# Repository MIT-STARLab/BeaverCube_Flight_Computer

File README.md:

# Note
This board is still under test, we will be updating system operational status as tests are completed.

# BFC
The BeaverCube Flight Computer, or CASTOR Pi Board, is an open-source flight computer for CubeSats. Designed for the MIT BeaverCube CubeSat mission, the board supports an imaging payload with 3 cameras over USB as well as subsystem boards over UART, I2C and SPI buses. 

CASTOR Pi Board: CubeSat Atmospheric and Sea-surface Temperature Optical Observation Raspberry Pi Board

# Known Issues, Testing Progress
The BFC rev 1.0 is currently being tested, with rev 2.0 expected to be manufactured and testing started by the end of August 2020. The power system has been characterized under expected loads and is fully operational with no errors detected. The RPI recovery system (see schematic Sheet 3) that controls which RPI is running and SD card is selected has been fully tested, and no errors detected.

The USB hub is currently under test to verify all ports can communicate with the compute module. Additional tests to be completed by mid-July 2020 include running flight software to verify all onboard devices (RTC, IMUs) function nominally, and interfacing the BFC with devices to test external connections including RS-485, TTL UART, I2C, SPI.

Known errors on rev 1.0 that will be fixed in rev 2.0
- SD card MUXs U4, U11, U13, U14 have incorrect footprints. The compute module cannot access the SD card slots.
- The USB line is routed to the incorrect GPIO pin on the compute module. A temporary fix was made to continue testing.

# project
Eagle CAD Project, Board, Schematic files.

# libraries
Ealgle CAD Library files.

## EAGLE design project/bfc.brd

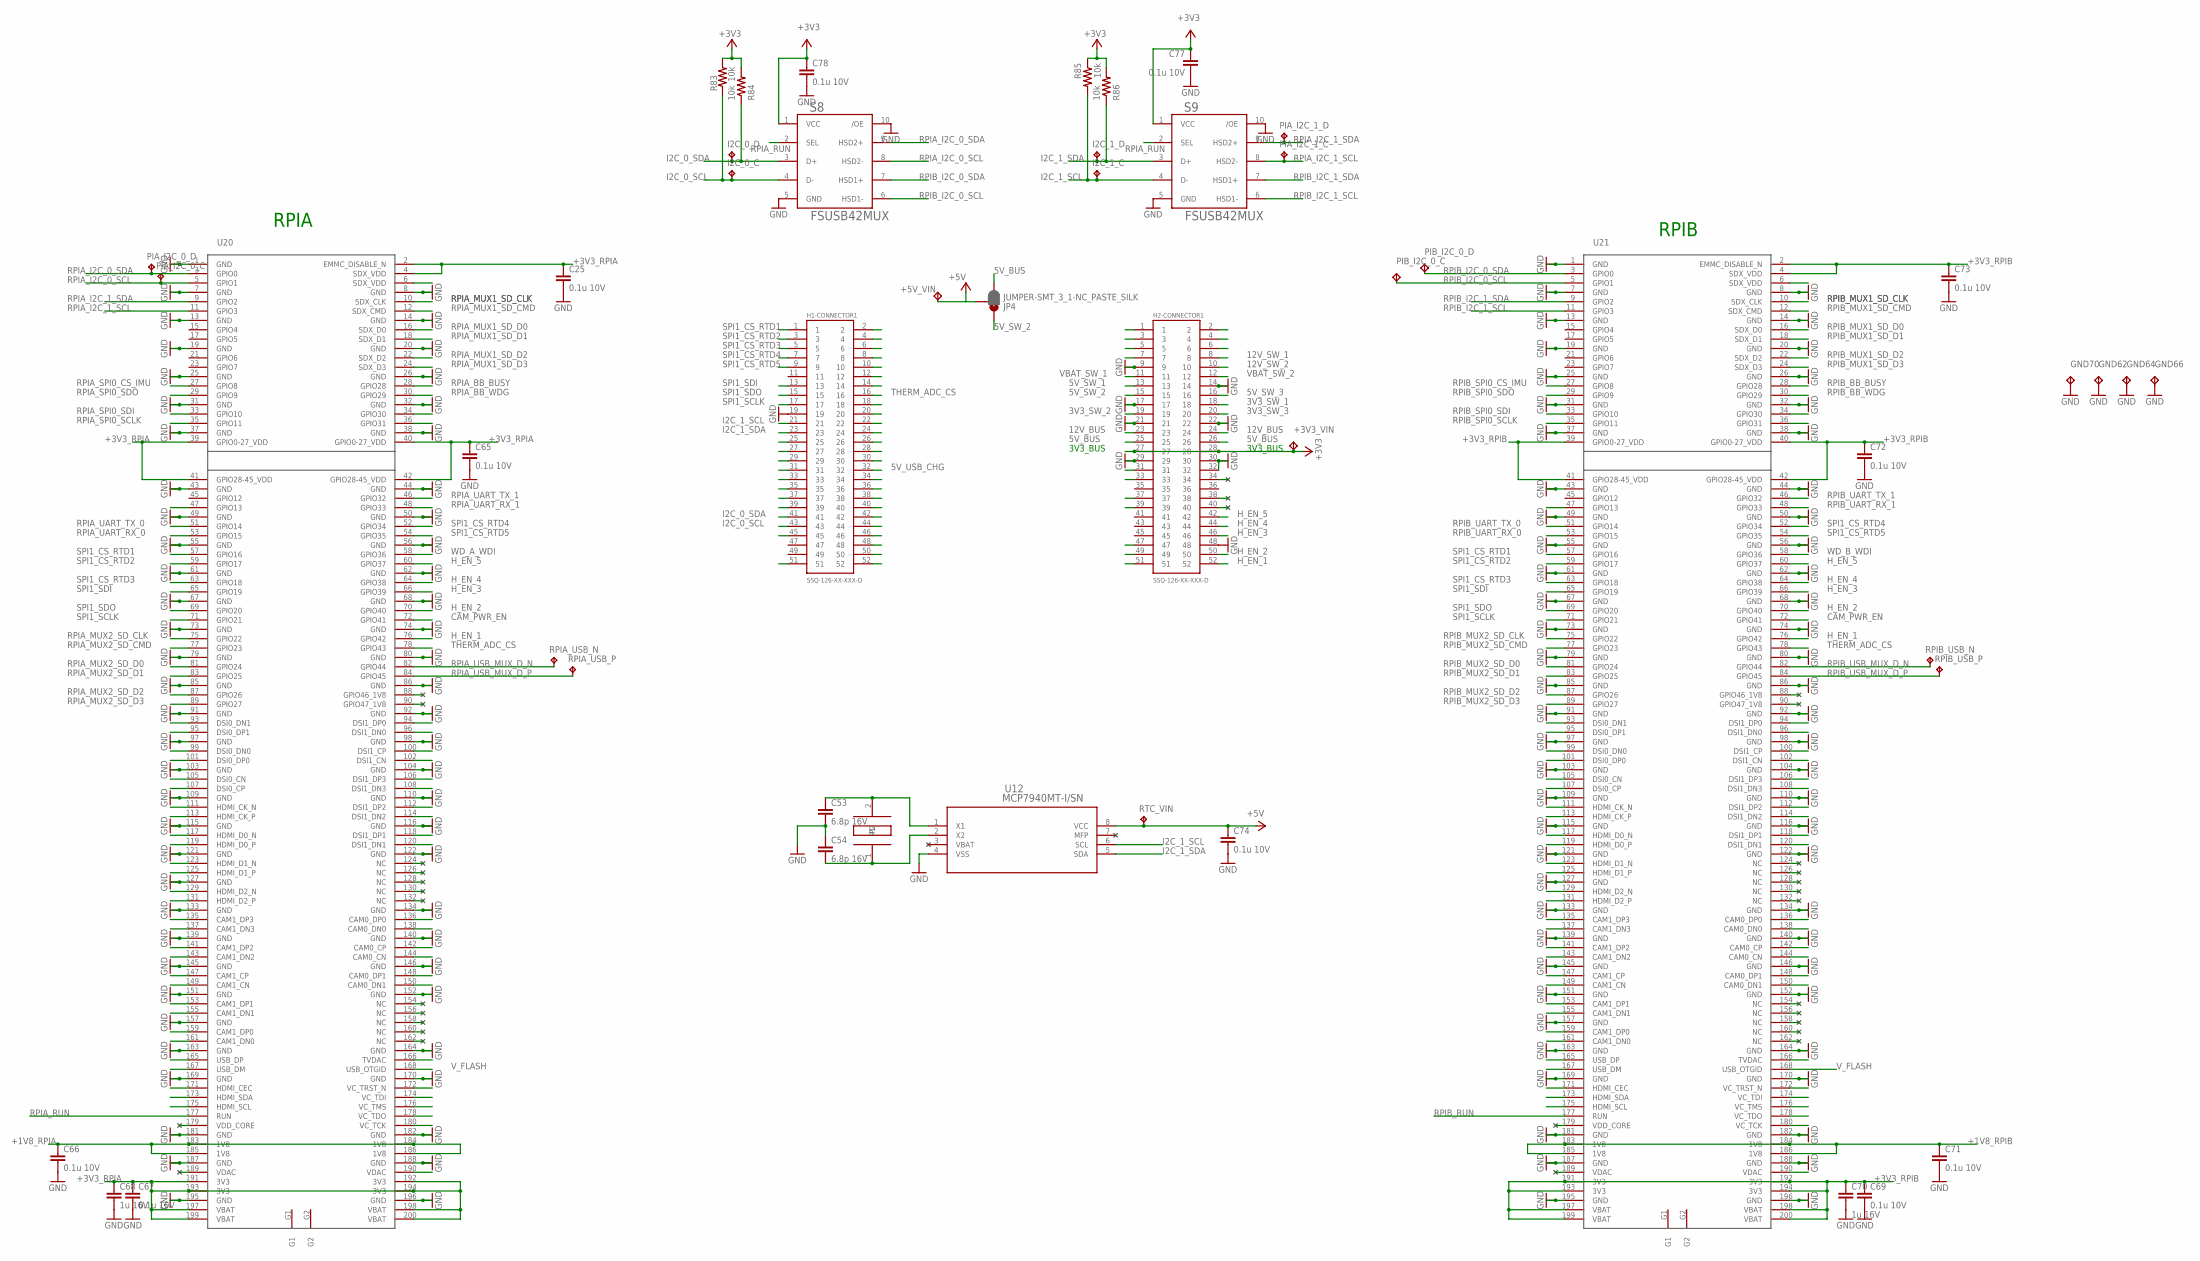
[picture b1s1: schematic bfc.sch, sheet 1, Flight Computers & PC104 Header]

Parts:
+3V3_VIN, +5V_VIN: TP_HRWN; MPN S2751-46R
C25, C65, C66, C67, C69, C71, C72, C73, C74, C77, C78: 0.1u 10V; C0603
C53, C54: 6.8p 16V; C0603
C68, C70: 1u 16V; C0603
GND62, GND64, GND66, GND70: TP_HRWN; MPN S2751-46R
H1-CONNECTOR1, H2-CONNECTOR1: SSQ-126-XX-XXX-D; MPN SSQ-126-23-G-D
I2C_0_C, I2C_0_D, I2C_1_C, I2C_1_D: TPB1,27; B1,27
JP4: JUMPER-SMT_3_1-NC_PASTE_SILK; SMT-JUMPER_3_1-NC_PASTE_SILK
PIA_I2C_0_C, PIA_I2C_0_D, PIA_I2C_1_C, PIA_I2C_1_D: TPB1,27; B1,27
PIB_I2C_0_C, PIB_I2C_0_D: TP_HRWN; MPN S2751-46R
R83, R84, R85, R86: 10k; R0603
RPIA_USB_N: TPB1,27; B1,27
RPIA_USB_P: TPB1,27; B1,27
RPIB_USB_N: TPB1,27; B1,27
RPIB_USB_P: TPB1,27; B1,27
RTC_VIN: TPB1,27; B1,27
S8, S9: FSUSB42MUX; MPN FSUSB42MUX
U12: MCP7940MT-I/SN; SOIC8-N_MC; MPN MCP7940MT-I/SN
U20, U21: COMPUTE_MODULE; SO-DIMM; MPN 1473005-4
X4: TC-135; MPN FC-135 32.768KA-AG0

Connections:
3V3_SW_1: H2-CONNECTOR1.18
3V3_SW_2: H2-CONNECTOR1.19; also elsewhere on the board
3V3_SW_3: H2-CONNECTOR1.20; also elsewhere on the board
5V_BUS: H2-CONNECTOR1.25, H2-CONNECTOR1.26, JP4.3; also elsewhere on the board
5V_SW_1: H2-CONNECTOR1.13
5V_SW_2: H2-CONNECTOR1.15, JP4.1
5V_SW_3: H2-CONNECTOR1.16
5V_USB_CHG: H1-CONNECTOR1.32
12V_BUS: H2-CONNECTOR1.23, H2-CONNECTOR1.24; also elsewhere on the board
12V_SW_1: H2-CONNECTOR1.8; also elsewhere on the board
12V_SW_2: H2-CONNECTOR1.10
+1V8_RPIA: C66.1, U20.183 (1V8), U20.184 (1V8), U20.185 (1V8), U20.186 (1V8); also elsewhere on the board
+1V8_RPIB: C71.1, U21.183 (1V8), U21.184 (1V8), U21.185 (1V8), U21.186 (1V8); also elsewhere on the board
+3V3: +3V3_VIN.P$1, C77.1, C78.1, H2-CONNECTOR1.27, H2-CONNECTOR1.28, R83.2, R84.2, R85.1, R86.2, S8.1 (VCC), S9.1 (VCC); also elsewhere on the board
+3V3_RPIA: C25.1, C65.1, C67.1, C68.1, U20.2 (EMMC_DISABLE_N), U20.4 (SDX_VDD), U20.39 (GPIO0-27_VDD), U20.40 (GPIO0-27_VDD), U20.41 (GPIO28-45_VDD), U20.42 (GPIO28-45_VDD), U20.191 (3V3), U20.192 (3V3), U20.193 (3V3), U20.194 (3V3), U20.197 (VBAT), U20.198 (VBAT), U20.199 (VBAT), U20.200 (VBAT); also elsewhere on the board
+3V3_RPIB: C69.1, C70.1, C72.1, C73.1, U21.2 (EMMC_DISABLE_N), U21.4 (SDX_VDD), U21.39 (GPIO0-27_VDD), U21.40 (GPIO0-27_VDD), U21.41 (GPIO28-45_VDD), U21.42 (GPIO28-45_VDD), U21.191 (3V3), U21.192 (3V3), U21.193 (3V3), U21.194 (3V3), U21.197 (VBAT), U21.198 (VBAT), U21.199 (VBAT), U21.200 (VBAT); also elsewhere on the board
+5V: +5V_VIN.P$1, C74.1, JP4.2, RTC_VIN.TP, U12.8 (VCC); also elsewhere on the board
CAM_PWR_EN: U20.72 (GPIO41), U21.72 (GPIO41); also elsewhere on the board
GND: C25.2, C53.2, C54.1, C65.2, C66.2, C67.2, C68.2, C69.2, C70.2, C71.2, C72.2, C73.2, C74.2, C77.2, C78.2, GND62.P$1, GND64.P$1, GND66.P$1, GND70.P$1, H1-CONNECTOR1.19, H2-CONNECTOR1.9, H2-CONNECTOR1.14, H2-CONNECTOR1.17, H2-CONNECTOR1.21, H2-CONNECTOR1.22, H2-CONNECTOR1.29, H2-CONNECTOR1.30, H2-CONNECTOR1.32, H2-CONNECTOR1.48, S8.5 (GND), S8.10 (/OE), S9.5 (GND), S9.10 (/OE), U12.4 (VSS), U20.1 (GND), U20.7 (GND), U20.8 (GND), U20.13 (GND), U20.14 (GND), U20.19 (GND), U20.20 (GND), U20.25 (GND), U20.26 (GND), U20.31 (GND), U20.32 (GND), U20.37 (GND), U20.38 (GND), U20.43 (GND), U20.44 (GND), U20.49 (GND), U20.50 (GND), U20.55 (GND), U20.56 (GND), U20.61 (GND), U20.62 (GND), U20.67 (GND), U20.68 (GND), U20.73 (GND), U20.74 (GND), U20.79 (GND), U20.80 (GND), U20.85 (GND), U20.86 (GND), U20.91 (GND), U20.92 (GND), U20.97 (GND), U20.98 (GND), U20.103 (GND), U20.104 (GND), U20.109 (GND), U20.110 (GND), U20.115 (GND), U20.116 (GND), U20.121 (GND), U20.122 (GND), U20.127 (GND), U20.133 (GND), U20.134 (GND), U20.139 (GND), U20.140 (GND), U20.145 (GND), U20.146 (GND), U20.151 (GND), U20.152 (GND), U20.157 (GND), U20.163 (GND), U20.164 (GND), U20.169 (GND), U20.170 (GND), U20.181 (GND), U20.182 (GND), U20.187 (GND), U20.188 (GND), U20.195 (GND), U20.196 (GND), U21.1 (GND), U21.7 (GND), U21.8 (GND), U21.13 (GND), U21.14 (GND), U21.19 (GND), U21.20 (GND), U21.25 (GND), U21.26 (GND), U21.31 (GND), U21.32 (GND), U21.37 (GND), U21.38 (GND), U21.43 (GND), U21.44 (GND), U21.49 (GND), U21.50 (GND), U21.55 (GND), U21.56 (GND), U21.61 (GND), U21.62 (GND), U21.67 (GND), U21.68 (GND), U21.73 (GND), U21.74 (GND), U21.79 (GND), U21.80 (GND), U21.85 (GND), U21.86 (GND), U21.91 (GND), U21.92 (GND), U21.97 (GND), U21.98 (GND), U21.103 (GND), U21.104 (GND), U21.109 (GND), U21.110 (GND), U21.115 (GND), U21.116 (GND), U21.121 (GND), U21.122 (GND), U21.127 (GND), U21.133 (GND), U21.134 (GND), U21.139 (GND), U21.140 (GND), U21.145 (GND), U21.146 (GND), U21.151 (GND), U21.152 (GND), U21.157 (GND), U21.163 (GND), U21.164 (GND), U21.169 (GND), U21.170 (GND), U21.181 (GND), U21.182 (GND), U21.187 (GND), U21.188 (GND), U21.195 (GND), U21.196 (GND); also elsewhere on the board
H_EN_1: H2-CONNECTOR1.52, U20.76 (GPIO42), U21.76 (GPIO42)
H_EN_2: H2-CONNECTOR1.50, U20.70 (GPIO40), U21.70 (GPIO40)
H_EN_3: H2-CONNECTOR1.46, U20.66 (GPIO39), U21.66 (GPIO39)
H_EN_4: H2-CONNECTOR1.44, U20.64 (GPIO38), U21.64 (GPIO38)
H_EN_5: H2-CONNECTOR1.42, U20.60 (GPIO37), U21.60 (GPIO37)
I2C_0_SCL: H1-CONNECTOR1.43, I2C_0_C.TP, R83.1, S8.4 (D-)
I2C_0_SDA: H1-CONNECTOR1.41, I2C_0_D.TP, R84.1, S8.3 (D+)
I2C_1_SCL: H1-CONNECTOR1.21, I2C_1_C.TP, R85.2, S9.4 (D-), U12.6 (SCL); also elsewhere on the board
I2C_1_SDA: H1-CONNECTOR1.23, I2C_1_D.TP, R86.1, S9.3 (D+), U12.5 (SDA); also elsewhere on the board
unnamed: C53.1, U12.1 (X1), X4.2
unnamed: C54.2, U12.2 (X2), X4.1
RPIA_BB_BUSY: U20.28 (GPIO28); also elsewhere on the board
RPIA_BB_WDG: U20.30 (GPIO29); also elsewhere on the board
RPIA_I2C_0_SCL: PIA_I2C_0_C.TP, S8.8 (HSD2-), U20.5 (GPIO1)
RPIA_I2C_0_SDA: PIA_I2C_0_D.TP, S8.9 (HSD2+), U20.3 (GPIO0)
RPIA_I2C_1_SCL: PIA_I2C_1_C.TP, S9.8 (HSD2-), U20.11 (GPIO3)
RPIA_I2C_1_SDA: PIA_I2C_1_D.TP, S9.9 (HSD2+), U20.9 (GPIO2)
RPIA_MUX1_SD_CLK: U20.10 (SDX_CLK); also elsewhere on the board
RPIA_MUX1_SD_CMD: U20.12 (SDX_CMD); also elsewhere on the board
RPIA_MUX1_SD_D0: U20.16 (SDX_D0); also elsewhere on the board
RPIA_MUX1_SD_D1: U20.18 (SDX_D1); also elsewhere on the board
RPIA_MUX1_SD_D2: U20.22 (SDX_D2); also elsewhere on the board
RPIA_MUX1_SD_D3: U20.24 (SDX_D3); also elsewhere on the board
RPIA_MUX2_SD_CLK: U20.75 (GPIO22); also elsewhere on the board
RPIA_MUX2_SD_CMD: U20.77 (GPIO23); also elsewhere on the board
RPIA_MUX2_SD_D0: U20.81 (GPIO24); also elsewhere on the board
RPIA_MUX2_SD_D1: U20.83 (GPIO25); also elsewhere on the board
RPIA_MUX2_SD_D2: U20.87 (GPIO26); also elsewhere on the board
RPIA_MUX2_SD_D3: U20.89 (GPIO27); also elsewhere on the board
RPIA_RUN: S8.2 (SEL), S9.2 (SEL), U20.177 (RUN); also elsewhere on the board
RPIA_SPI0_CS_IMU: U20.27 (GPIO8); also elsewhere on the board
RPIA_SPI0_SCLK: U20.35 (GPIO11); also elsewhere on the board
RPIA_SPI0_SDI: U20.33 (GPIO10); also elsewhere on the board
RPIA_SPI0_SDO: U20.29 (GPIO9); also elsewhere on the board
RPIA_UART_RX_0: U20.53 (GPIO15); also elsewhere on the board
RPIA_UART_RX_1: U20.48 (GPIO33); also elsewhere on the board
RPIA_UART_TX_0: U20.51 (GPIO14); also elsewhere on the board
RPIA_UART_TX_1: U20.46 (GPIO32); also elsewhere on the board
RPIA_USB_MUX_D_N: RPIA_USB_N.TP, U20.82 (GPIO44); also elsewhere on the board
RPIA_USB_MUX_D_P: RPIA_USB_P.TP, U20.84 (GPIO45); also elsewhere on the board
RPIB_BB_BUSY: U21.28 (GPIO28); also elsewhere on the board
RPIB_BB_WDG: U21.30 (GPIO29); also elsewhere on the board
RPIB_I2C_0_SCL: PIB_I2C_0_C.P$1, S8.6 (HSD1-), U21.5 (GPIO1)
RPIB_I2C_0_SDA: PIB_I2C_0_D.P$1, S8.7 (HSD1+), U21.3 (GPIO0)
RPIB_I2C_1_SCL: S9.6 (HSD1-), U21.11 (GPIO3)
RPIB_I2C_1_SDA: S9.7 (HSD1+), U21.9 (GPIO2)
RPIB_MUX1_SD_CLK: U21.10 (SDX_CLK); also elsewhere on the board
RPIB_MUX1_SD_CMD: U21.12 (SDX_CMD); also elsewhere on the board
RPIB_MUX1_SD_D0: U21.16 (SDX_D0); also elsewhere on the board
RPIB_MUX1_SD_D1: U21.18 (SDX_D1); also elsewhere on the board
RPIB_MUX1_SD_D2: U21.22 (SDX_D2); also elsewhere on the board
RPIB_MUX1_SD_D3: U21.24 (SDX_D3); also elsewhere on the board
RPIB_MUX2_SD_CLK: U21.75 (GPIO22); also elsewhere on the board
RPIB_MUX2_SD_CMD: U21.77 (GPIO23); also elsewhere on the board
RPIB_MUX2_SD_D0: U21.81 (GPIO24); also elsewhere on the board
RPIB_MUX2_SD_D1: U21.83 (GPIO25); also elsewhere on the board
RPIB_MUX2_SD_D2: U21.87 (GPIO26); also elsewhere on the board
RPIB_MUX2_SD_D3: U21.89 (GPIO27); also elsewhere on the board
RPIB_RUN: U21.177 (RUN); also elsewhere on the board
RPIB_SPI0_CS_IMU: U21.27 (GPIO8); also elsewhere on the board
RPIB_SPI0_SCLK: U21.35 (GPIO11); also elsewhere on the board
RPIB_SPI0_SDI: U21.33 (GPIO10); also elsewhere on the board
RPIB_SPI0_SDO: U21.29 (GPIO9); also elsewhere on the board
RPIB_UART_RX_0: U21.53 (GPIO15); also elsewhere on the board
RPIB_UART_RX_1: U21.48 (GPIO33); also elsewhere on the board
RPIB_UART_TX_0: U21.51 (GPIO14); also elsewhere on the board
RPIB_UART_TX_1: U21.46 (GPIO32); also elsewhere on the board
RPIB_USB_MUX_D_N: RPIB_USB_N.TP, U21.82 (GPIO44); also elsewhere on the board
RPIB_USB_MUX_D_P: RPIB_USB_P.TP, U21.84 (GPIO45); also elsewhere on the board
SPI1_CS_RTD1: H1-CONNECTOR1.1, U20.57 (GPIO16), U21.57 (GPIO16)
SPI1_CS_RTD2: H1-CONNECTOR1.3, U20.59 (GPIO17), U21.59 (GPIO17)
SPI1_CS_RTD3: H1-CONNECTOR1.5, U20.63 (GPIO18), U21.63 (GPIO18)
SPI1_CS_RTD4: H1-CONNECTOR1.7, U20.52 (GPIO34), U21.52 (GPIO34)
SPI1_CS_RTD5: H1-CONNECTOR1.9, U20.54 (GPIO35), U21.54 (GPIO35)
SPI1_SCLK: H1-CONNECTOR1.17, U20.71 (GPIO21), U21.71 (GPIO21)
SPI1_SDI: H1-CONNECTOR1.13, U20.65 (GPIO19), U21.65 (GPIO19)
SPI1_SDO: H1-CONNECTOR1.15, U20.69 (GPIO20), U21.69 (GPIO20)
THERM_ADC_CS: H1-CONNECTOR1.16, U20.78 (GPIO43), U21.78 (GPIO43)
VBAT: U12.3 (VBAT)
VBAT_SW_1: H2-CONNECTOR1.11
VBAT_SW_2: H2-CONNECTOR1.12
V_FLASH: U20.168 (USB_OTGID), U21.168 (USB_OTGID); also elsewhere on the board
WD_A_WDI: U20.58 (GPIO36); also elsewhere on the board
WD_B_WDI: U21.58 (GPIO36); also elsewhere on the board

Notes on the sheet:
RPIA
RPIB
3V3_BUS

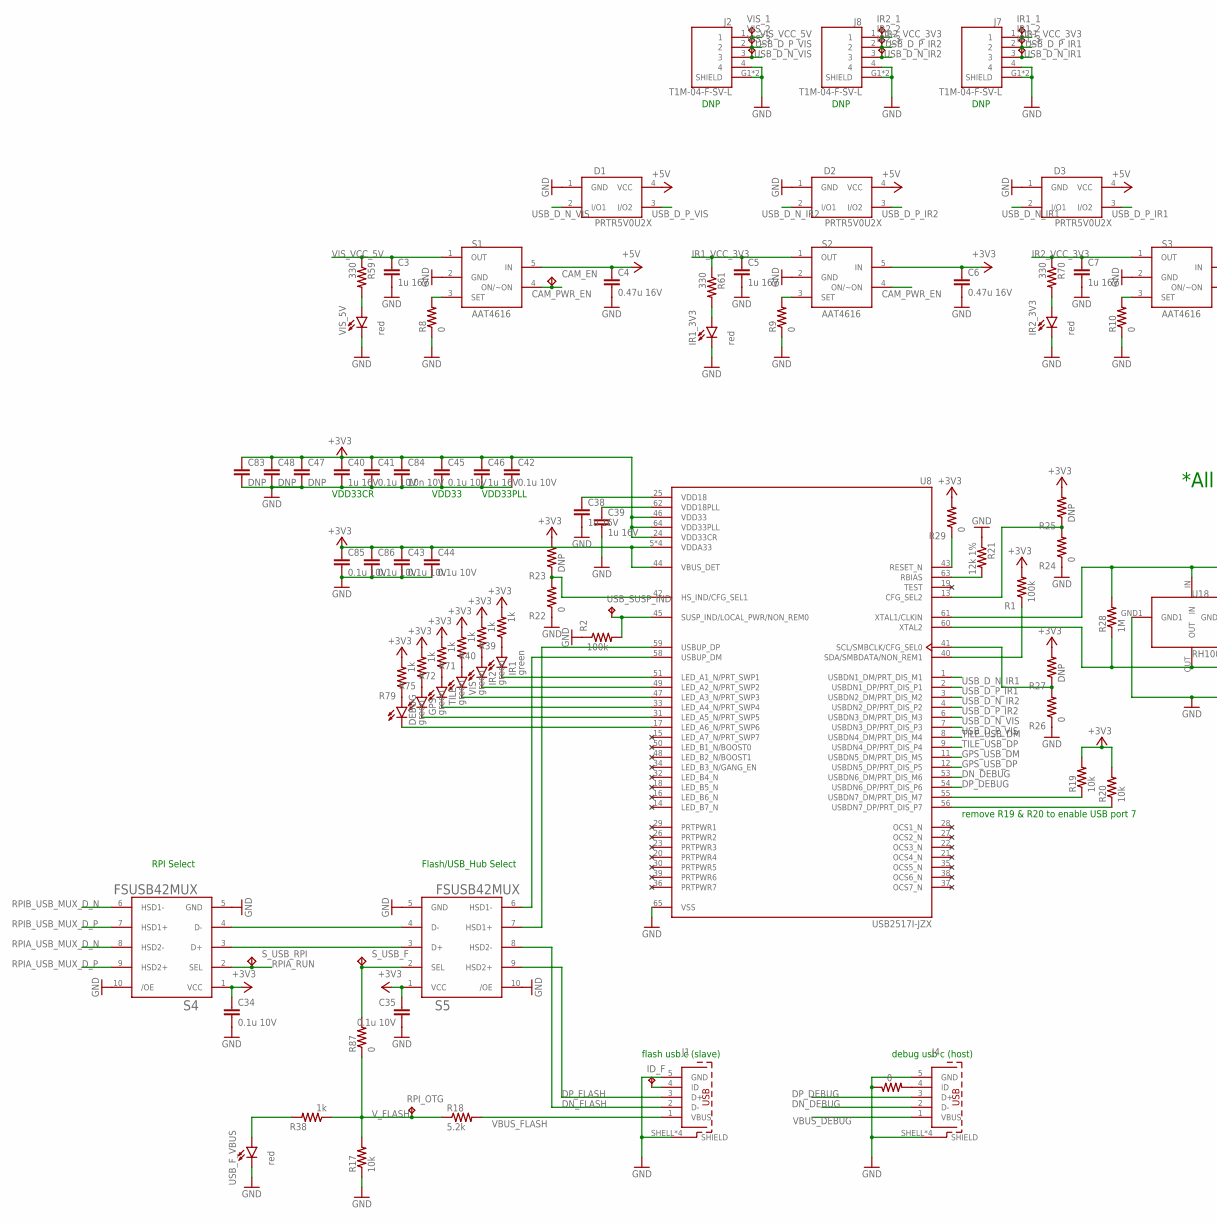
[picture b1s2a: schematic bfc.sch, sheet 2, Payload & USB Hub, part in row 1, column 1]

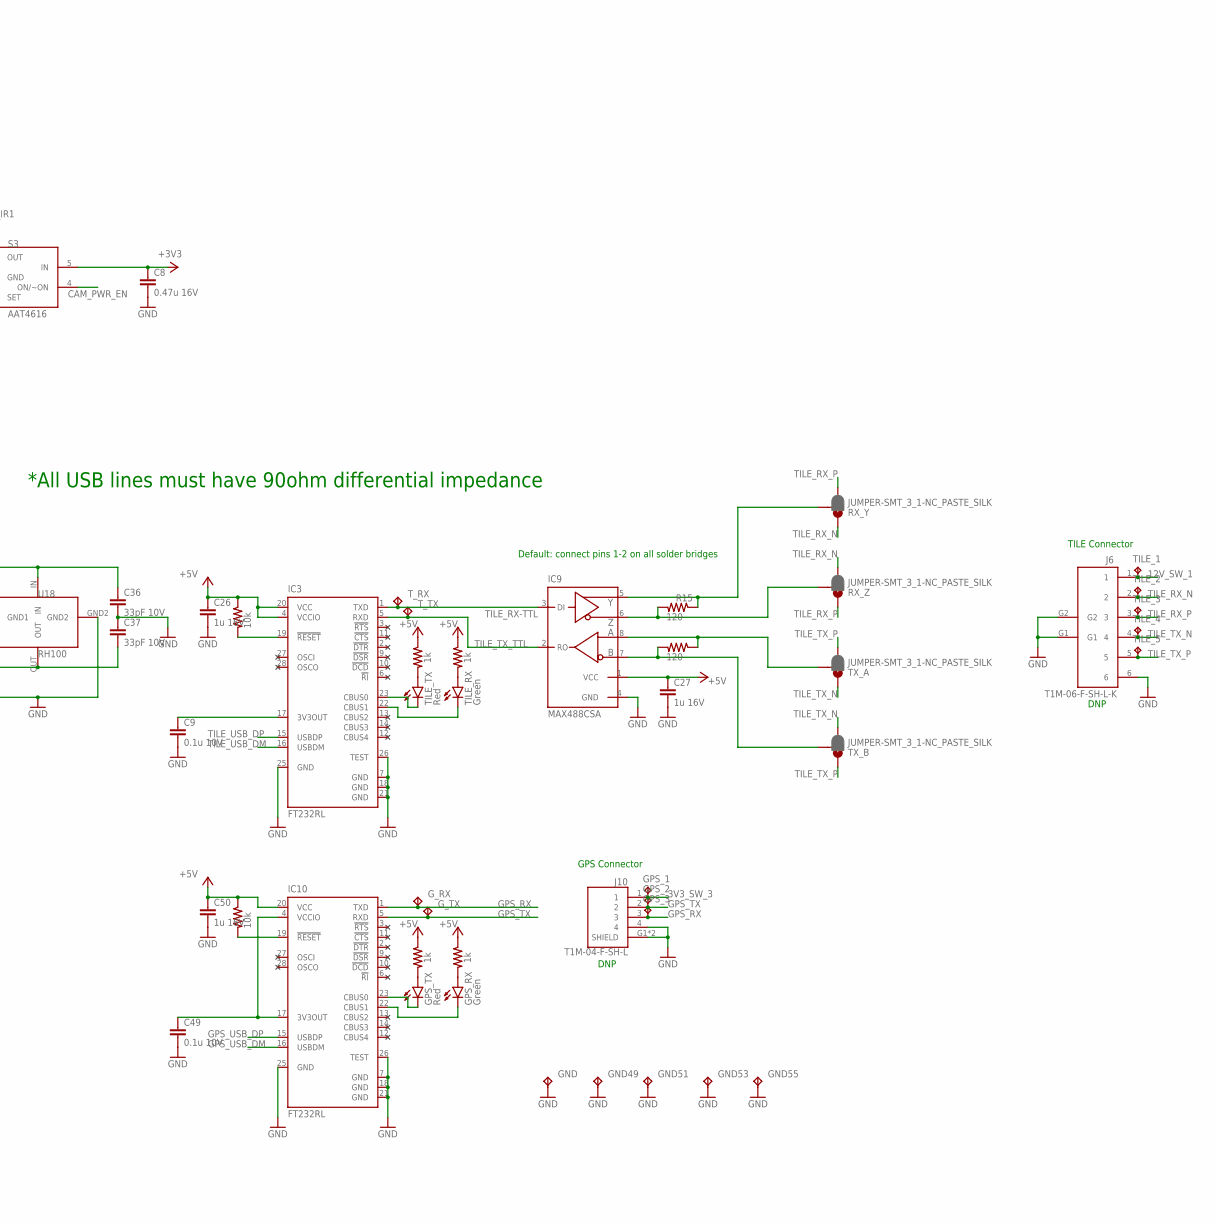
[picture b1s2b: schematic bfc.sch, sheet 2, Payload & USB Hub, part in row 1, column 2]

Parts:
C3, C5, C7, C26, C27, C38, C39, C40, C46, C50: 1u 16V; C0603
C4, C6, C8: 0.47u 16V; C0603
C9, C34, C35, C41, C42, C43, C44, C45, C49, C85, C86: 0.1u 10V; C0603
C36, C37: 33pF 10V; C0603
C47, C48, C83: DNP; C0603
C84: 10n 10V; C0603
CAM_EN: TP_HRWN
D1, D2, D3: PRTR5V0U2X; MPN PRTR5V0U2X,215
DEBUG: green; SML0603; MPN LG L29K-F2J1-24-Z
GND, GND49, GND51, GND53, GND55: TP_HRWN
GPS: green; SML0603; MPN LG L29K-F2J1-24-Z
GPS_1, GPS_2, GPS_3: TPTP15SQ; TP15SQ
GPS_RX: Green; SML0603; MPN 150060VS75000
GPS_TX: Red; SML0603; MPN LTST-C190CKT
G_RX: TP_HRWN
G_TX: TP_HRWN
IC3, IC10: FT232RL; SSOP28
IC9: MAX488CSA; SO08; MPN MAX488ESA+
ID_F: TPTP18SQ; TP18SQ
IR1, IR2: green; SML0603; MPN LG L29K-F2J1-24-Z
IR1_1, IR1_2, IR1_3, IR2_1, IR2_2, IR2_3: TPTP15SQ; TP15SQ
IR1_3V3, IR2_3V3: red; SML0603; MPN LTST-C190CKT
J1, J4: 629105150521; MPN 629105150521
J2, J7, J8: T1M-04-F-SV-L; SAMTEC_T1M-04-F-SV-L; MPN T1M-04-F-SV-L
J6: T1M-06-F-SH-L-K; MPN T1M-06-F-SH-L
J10: T1M-04-F-SH-L; SAMTEC_T1M-04-F-SH-L; MPN T1M-04-F-SH-L
R1, R2: 100k; R0603
R8, R9, R10, R24, R26, R37: 0; R0603
R11, R17, R19, R20, R31: 10k; R0603
R12, R30, R32, R33, R38, R39, R40, R71, R72, R75, R79: 1k; R0603
R15, R16: 120; R0603
R18: 5.2k; R0805
R21: 12k 1%; R0603
R22, R29, R87: 0; R0805
R23: DNP; R0805
R25, R27: DNP; R0603
R28: 1M; R0603
R59, R61, R70: 330; R0603
RPI_OTG: TPB1,27; B1,27
RX_Y: JUMPER-SMT_3_1-NC_PASTE_SILK; SMT-JUMPER_3_1-NC_PASTE_SILK
RX_Z: JUMPER-SMT_3_1-NC_PASTE_SILK; SMT-JUMPER_3_1-NC_PASTE_SILK
S1, S2, S3: AAT4616; MPN AAT4616IGV-T1
S4, S5: FSUSB42MUX; MPN FSUSB42MUX
S_USB_F: TP_HRWN
S_USB_RPI: TP_HRWN
TILE: green; SML0603; MPN LG L29K-F2J1-24-Z
TILE_1, TILE_2, TILE_3, TILE_4, TILE_5: TPTP15SQ; TP15SQ
TILE_RX: Green; SML0603; MPN 150060VS75000
TILE_TX: Red; SML0603; MPN LTST-C190CKT
TX_A: JUMPER-SMT_3_1-NC_PASTE_SILK; SMT-JUMPER_3_1-NC_PASTE_SILK
TX_B: JUMPER-SMT_3_1-NC_PASTE_SILK; SMT-JUMPER_3_1-NC_PASTE_SILK
T_RX: TP_HRWN
T_TX: TP_HRWN
U8: USB2517I-JZX; QFN50P900X900X100-65N; MPN USB2517I-JZX-TR
U18: RH100; MPN RH100-24.000-20-3050-EXT-TR
USB_F_VBUS: red; SML0603; MPN LTST-C190CKT
USB_SUSP_IND: TPTP18SQ; TP18SQ
VIS: green; SML0603; MPN LG L29K-F2J1-24-Z
VIS_1, VIS_2, VIS_3: TPTP15SQ; TP15SQ
VIS_5V: red; SML0603; MPN LTST-C190CKT

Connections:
3V3_SW_3: GPS_1.TP, J10.1; also elsewhere on the board
12V_SW_1: J6.1, TILE_1.TP; also elsewhere on the board
+3V3: C6.1, C8.1, C34.1, C35.1, C40.1, C41.1, C42.1, C43.1, C44.1, C45.1, C46.1, C47.1, C48.1, C83.1, C84.1, C85.1, C86.1, R1.2, R19.2, R20.2, R23.2, R25.2, R27.2, R29.2, R39.2, R40.2, R71.2, R72.2, R75.2, R79.2, S2.5 (IN), S3.5 (IN), S4.1 (VCC), S5.1 (VCC), U8.5 (VDDA33), U8.10 (VDDA33), U8.24 (VDD33CR), U8.44 (VBUS_DET), U8.46 (VDD33), U8.52 (VDDA33), U8.57 (VDDA33), U8.64 (VDD33PLL); also elsewhere on the board
+5V: C4.1, C26.1, C27.1, C50.1, D1.4 (VCC), D2.4 (VCC), D3.4 (VCC), IC3.4 (VCCIO), IC3.20 (VCC), IC9.1 (VCC), IC10.20 (VCC), R11.1, R12.1, R30.1, R31.1, R32.1, R33.1, S1.5 (IN); also elsewhere on the board
CAM_PWR_EN: CAM_EN.P$1, S1.4 (ON/~ON), S2.4 (ON/~ON), S3.4 (ON/~ON); also elsewhere on the board
DN_DEBUG: J4.2 (D-), U8.53 (USBDN6_DM/PRT_DIS_M6)
DN_FLASH: J1.2 (D-), S5.8 (HSD2-)
DP_DEBUG: J4.3 (D+), U8.54 (USBDN6_DP/PRT_DIS_P6)
DP_FLASH: J1.3 (D+), S5.9 (HSD2+)
GND: C3.2, C4.2, C5.2, C6.2, C7.2, C8.2, C9.2, C26.2, C27.2, C34.2, C35.2, C36.2, C37.1, C38.2, C39.2, C40.2, C41.2, C42.2, C43.2, C44.2, C45.2, C46.2, C47.2, C48.2, C49.2, C50.2, C83.2, C84.2, C85.2, C86.2, D1.1 (GND), D2.1 (GND), D3.1 (GND), GND.P$1, GND49.P$1, GND51.P$1, GND53.P$1, GND55.P$1, IC3.7 (GND), IC3.18 (GND), IC3.21 (GND), IC3.25 (GND), IC3.26 (TEST), IC9.4 (GND), IC10.7 (GND), IC10.18 (GND), IC10.21 (GND), IC10.25 (GND), IC10.26 (TEST), IR1_3V3.C, IR2_3V3.C, J1.5 (GND), J1.SHELL (SHIELD), J1.SHELL1 (SHIELD), J1.SHELL2 (SHIELD), J1.SHELL3 (SHIELD), J2.4, J2.G1 (SHIELD), J2.G2 (SHIELD), J4.5 (GND), J4.SHELL (SHIELD), J4.SHELL1 (SHIELD), J4.SHELL2 (SHIELD), J4.SHELL3 (SHIELD), J6.6, J6.G1, J6.G2, J7.4, J7.G1 (SHIELD), J7.G2 (SHIELD), J8.4, J8.G1 (SHIELD), J8.G2 (SHIELD), J10.4, J10.G1 (SHIELD), J10.G2 (SHIELD), R2.1, R8.1, R9.1, R10.1, R17.1, R21.1, R22.1, R24.1, R26.1, R37.1, S1.2 (GND), S2.2 (GND), S3.2 (GND), S4.5 (GND), S4.10 (/OE), S5.5 (GND), S5.10 (/OE), U8.65 (VSS), U18.GND1, U18.GND2, USB_F_VBUS.C, VIS_5V.C; also elsewhere on the board
GPS_RX: GPS_3.TP, G_RX.P$1, IC10.1 (TXD), J10.3
GPS_TX: GPS_2.TP, G_TX.P$1, IC10.5 (RXD), J10.2
GPS_USB_DM: IC10.16 (USBDM), U8.11 (USBDN5_DM/PRT_DIS_M5)
GPS_USB_DP: IC10.15 (USBDP), U8.12 (USBDN5_DP/PRT_DIS_P5)
IR1_VCC_3V3: C5.1, IR1_1.TP, J7.1, R61.1, S2.1 (OUT)
IR2_VCC_3V3: C7.1, IR2_1.TP, J8.1, R70.1, S3.1 (OUT)
unnamed: R10.2, S3.3 (SET)
unnamed: R8.2, S1.3 (SET)
unnamed: R9.2, S2.3 (SET)
unnamed: R22.2, R23.1, U8.42 (HS_IND/CFG_SEL1)
unnamed: J4.4 (ID), R37.2
unnamed: R38.2, USB_F_VBUS.A
unnamed: IR1.A, R39.1
unnamed: IR1.C, U8.51 (LED_A1_N/PRT_SWP1)
unnamed: IC3.19 (!RESET), R11.2
unnamed: R12.2, TILE_TX.A
unnamed: R30.2, TILE_RX.A
unnamed: IC3.23 (CBUS0), TILE_TX.C
unnamed: IC9.7 (B), R16.2, TX_B.2
unnamed: IC3.22 (CBUS1), TILE_RX.C
unnamed: C9.1, IC3.17 (3V3OUT)
unnamed: IC10.19 (!RESET), R31.2
unnamed: GPS_TX.A, R32.2
unnamed: IR2.C, U8.49 (LED_A2_N/PRT_SWP2)
unnamed: IR2.A, R40.1
unnamed: R71.1, VIS.A
unnamed: R72.1, TILE.A
unnamed: GPS.A, R75.1
unnamed: DEBUG.A, R79.1
unnamed: U8.47 (LED_A3_N/PRT_SWP3), VIS.C
unnamed: TILE.C, U8.33 (LED_A4_N/PRT_SWP4)
unnamed: GPS.C, U8.31 (LED_A5_N/PRT_SWP5)
unnamed: R21.2, U8.63 (RBIAS)
unnamed: DEBUG.C, U8.17 (LED_A6_N/PRT_SWP6)
unnamed: R87.2, S5.2 (SEL), S_USB_F.P$1
unnamed: IC9.5 (Y), R15.1, RX_Y.2
unnamed: GPS_RX.A, R33.2
unnamed: GPS_TX.C, IC10.23 (CBUS0)
unnamed: GPS_RX.C, IC10.22 (CBUS1)
unnamed: ID_F.TP, J1.4 (ID)
unnamed: R1.1, U8.40 (SDA/SMBDATA/NON_REM1)
unnamed: S4.3 (D+), S5.3 (D+)
unnamed: S4.4 (D-), S5.4 (D-)
unnamed: R26.2, R27.1, U8.41 (SCL/SMBCLK/CFG_SEL0)
unnamed: S5.6 (HSD1-), U8.58 (USBUP_DM)
unnamed: S5.7 (HSD1+), U8.59 (USBUP_DP)
unnamed: R19.1, U8.55 (USBDN7_DM/PRT_DIS_M7)
unnamed: R20.1, U8.56 (USBDN7_DP/PRT_DIS_P7)
unnamed: R24.2, R25.1, U8.13 (CFG_SEL2)
unnamed: C36.1, R28.2, U8.61 (XTAL1/CLKIN), U18.IN
unnamed: C49.1, IC10.4 (VCCIO), IC10.17 (3V3OUT)
unnamed: C38.1, U8.25 (VDD18)
unnamed: C37.2, R28.1, U8.60 (XTAL2), U18.OUT
unnamed: C39.1, U8.62 (VDD18PLL)
unnamed: R2.2, U8.45 (SUSP_IND/LOCAL_PWR/NON_REM0), USB_SUSP_IND.TP
unnamed: R29.1, U8.43 (RESET_N)
unnamed: IC9.6 (Z), R15.2, RX_Z.2
unnamed: IC9.8 (A), R16.1, TX_A.2
unnamed: IR1_3V3.A, R61.2
unnamed: IR2_3V3.A, R70.2
unnamed: R59.2, VIS_5V.A
RPIA_RUN: S4.2 (SEL), S_USB_RPI.P$1; also elsewhere on the board
RPIA_USB_MUX_D_N: S4.8 (HSD2-); also elsewhere on the board
RPIA_USB_MUX_D_P: S4.9 (HSD2+); also elsewhere on the board
RPIB_USB_MUX_D_N: S4.6 (HSD1-); also elsewhere on the board
RPIB_USB_MUX_D_P: S4.7 (HSD1+); also elsewhere on the board
TILE_RX-TTL: IC3.1 (TXD), IC9.3 (DI), T_RX.P$1
TILE_RX_N: J6.2, RX_Y.1, RX_Z.3, TILE_2.TP
TILE_RX_P: J6.3, RX_Y.3, RX_Z.1, TILE_3.TP
TILE_TX_N: J6.4, TILE_4.TP, TX_A.1, TX_B.3
TILE_TX_P: J6.5, TILE_5.TP, TX_A.3, TX_B.1
TILE_TX_TTL: IC3.5 (RXD), IC9.2 (RO), T_TX.P$1
TILE_USB_DM: IC3.16 (USBDM), U8.8 (USBDN4_DM/PRT_DIS_M4)
TILE_USB_DP: IC3.15 (USBDP), U8.9 (USBDN4_DP/PRT_DIS_P4)
USB_D_N_IR1: D3.2 (I/O1), IR1_3.TP, J7.3, U8.1 (USBDN1_DM/PRT_DIS_M1)
USB_D_N_IR2: D2.2 (I/O1), IR2_3.TP, J8.3, U8.3 (USBDN2_DM/PRT_DIS_M2)
USB_D_N_VIS: D1.2 (I/O1), J2.3, U8.6 (USBDN3_DM/PRT_DIS_M3), VIS_3.TP
USB_D_P_IR1: D3.3 (I/O2), IR1_2.TP, J7.2, U8.2 (USBDN1_DP/PRT_DIS_P1)
USB_D_P_IR2: D2.3 (I/O2), IR2_2.TP, J8.2, U8.4 (USBDN2_DP/PRT_DIS_P2)
USB_D_P_VIS: D1.3 (I/O2), J2.2, U8.7 (USBDN3_DP/PRT_DIS_P3), VIS_2.TP
VBUS_DEBUG: J4.1 (VBUS)
VBUS_FLASH: J1.1 (VBUS), R18.2
VIS_VCC_5V: C3.1, J2.1, R59.1, S1.1 (OUT), VIS_1.TP
V_FLASH: R17.2, R18.1, R38.1, R87.1, RPI_OTG.TP; also elsewhere on the board

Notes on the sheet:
Flash/USB_Hub Select
RPI Select
remove R19 & R20 to enable USB port 7
Default: connect pins 1-2 on all solder bridges
debug usb c (host)
*All USB lines must have 90ohm differential impedance
TILE Connector
GPS Connector
VDD33CR
VDD33
VDD33PLL
flash usb c (slave)
DNP

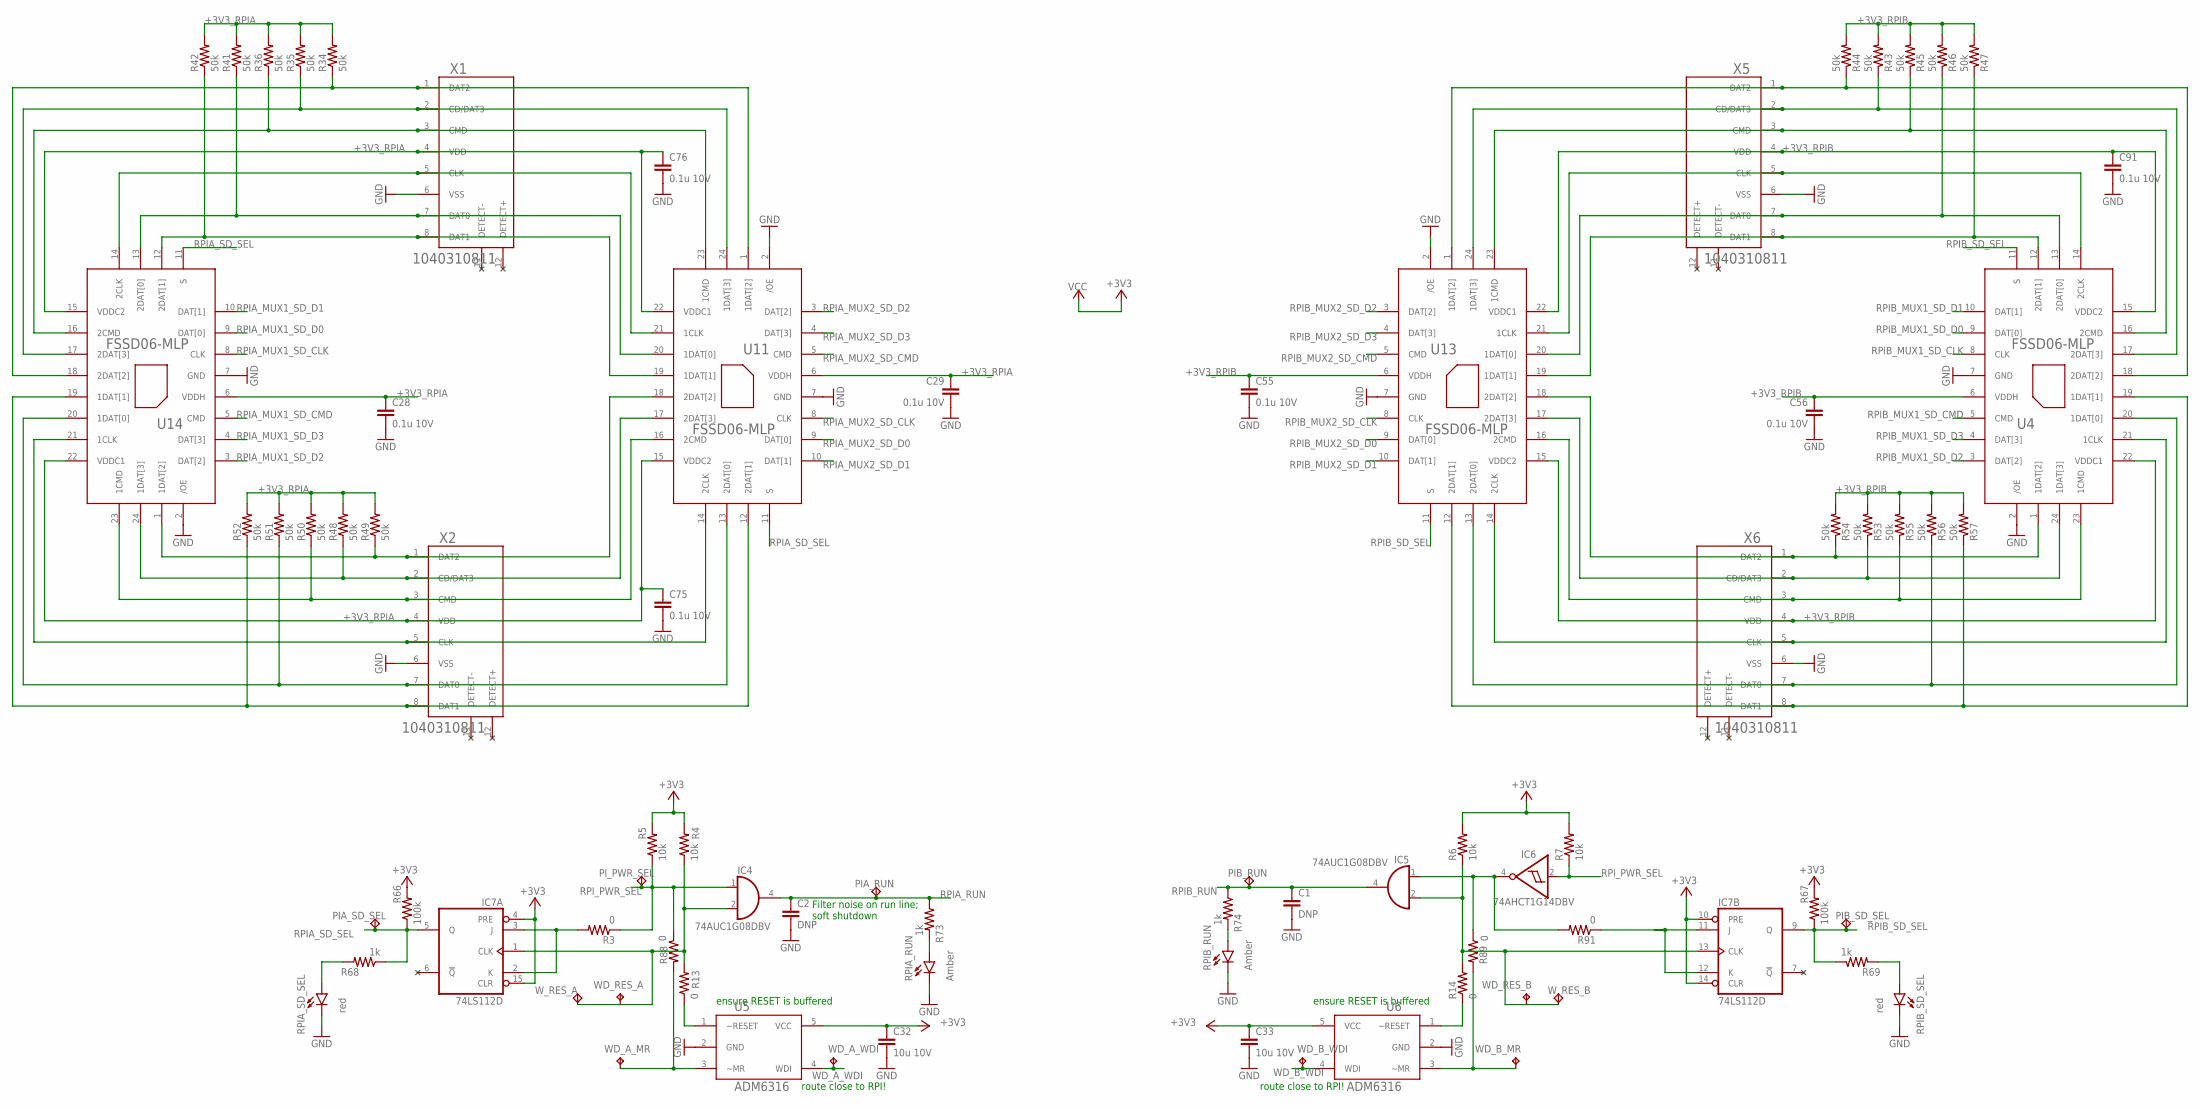
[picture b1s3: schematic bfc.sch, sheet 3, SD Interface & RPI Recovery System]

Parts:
C1, C2: DNP; C0603
C28, C29, C55, C56, C75, C76, C91: 0.1u 10V; C0603
C32, C33: 10u 10V; C0805
IC4, IC5: 74AUC1G08DBV; SOT23-5; MPN SN74LVC1G08MDBVREP
IC6: 74AHCT1G14DBV; SOT23-5; MPN SN74LVC1G14MDBVREP
IC7: 74LS112D; SO16; MPN SN74LVC112ADR
PIA_RUN: TP_HRWN; MPN S2751-46R
PIA_SD_SEL: TP_HRWN; MPN S2751-46R
PIB_RUN: TP_HRWN; MPN S2751-46R
PIB_SD_SEL: TP_HRWN; MPN S2751-46R
PI_PWR_SEL: TP_HRWN; MPN S2751-46R
R3, R13, R14, R88, R89, R91: 0; R0603
R4, R5, R6, R7: 10k; R0603
R34, R35, R36, R41, R42, R43, R44, R45, R46, R47, R48, R49, R50, R51, R52, R53, R54, R55, R56, R57: 50k; R0603
R66, R67: 100k; R0603
R68, R69, R73, R74: 1k; R0603
RPIA_RUN: Amber; SML0603; MPN SM0805AC
RPIA_SD_SEL: red; SML0603; MPN LTST-C190CKT
RPIB_RUN: Amber; SML0603; MPN SM0805AC
RPIB_SD_SEL: red; SML0603; MPN LTST-C190CKT
U4, U11, U13, U14: FSSD06-MLP; MPN FSSD06BQX
U5, U6: ADM6316; AMD6316; MPN ADM6320CZ29ARJZ-R7
WD_A_MR: TPTP18SQ; TP18SQ
WD_A_WDI: TPB1,27; B1,27
WD_B_MR: TPTP18SQ; TP18SQ
WD_B_WDI: TPB1,27; B1,27
WD_RES_A: TPTP18SQ; TP18SQ
WD_RES_B: TPTP18SQ; TP18SQ
W_RES_A: TP_HRWN; MPN S2751-46R
W_RES_B: TP_HRWN; MPN S2751-46R
X1, X2, X5, X6: 1040310811; MPN 1040310811

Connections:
+3V3: C32.1, C33.1, IC4.5 (VCC), IC5.5 (VCC), IC6.5 (VCC), IC7.4 (PRE), IC7.10 (PRE), IC7.14 (CLR), IC7.15 (CLR), IC7.16 (VCC), R4.2, R5.2, R6.2, R7.2, R66.2, R67.2, U5.5 (VCC), U6.5 (VCC); also elsewhere on the board
+3V3_RPIA: C28.1, C29.1, C75.1, C76.1, R34.2, R35.2, R36.2, R41.2, R42.2, R48.2, R49.2, R50.2, R51.2, R52.2, U11.6 (VDDH), U11.15 (VDDC2), U11.22 (VDDC1), U14.6 (VDDH), U14.15 (VDDC2), U14.22 (VDDC1), X1.4 (VDD), X2.4 (VDD); also elsewhere on the board
+3V3_RPIB: C55.1, C56.1, C91.1, R43.2, R44.2, R45.2, R46.2, R47.2, R53.2, R54.2, R55.2, R56.2, R57.2, U4.6 (VDDH), U4.15 (VDDC2), U4.22 (VDDC1), U13.6 (VDDH), U13.15 (VDDC2), U13.22 (VDDC1), X5.4 (VDD), X6.4 (VDD); also elsewhere on the board
GND: C1.2, C2.2, C28.2, C29.2, C32.2, C33.2, C55.2, C56.2, C75.2, C76.2, C91.2, IC4.3 (GND), IC5.3 (GND), IC6.3 (GND), IC7.8 (GND), RPIA_RUN.C, RPIA_SD_SEL.C, RPIB_RUN.C, RPIB_SD_SEL.C, U4.2 (/OE), U4.7 (GND), U5.2 (GND), U6.2 (GND), U11.2 (/OE), U11.7 (GND), U13.2 (/OE), U13.7 (GND), U14.2 (/OE), U14.7 (GND), X1.6 (VSS), X2.6 (VSS), X5.6 (VSS), X6.6 (VSS); also elsewhere on the board
unnamed: R34.1, U11.1 (1DAT[2]), U14.18 (2DAT[2]), X1.1 (DAT2)
unnamed: R35.1, U11.24 (1DAT[3]), U14.17 (2DAT[3]), X1.2 (CD/DAT3)
unnamed: R36.1, U11.23 (1CMD), U14.16 (2CMD), X1.3 (CMD)
unnamed: IC7.2 (K), IC7.3 (J), R3.2
unnamed: IC7.11 (J), IC7.12 (K), R91.1
unnamed: R88.2, U5.3 (~MR), WD_A_MR.TP
unnamed: R89.2, U6.3 (~MR), WD_B_MR.TP
unnamed: U11.21 (1CLK), U14.14 (2CLK), X1.5 (CLK)
unnamed: R41.1, U11.20 (1DAT[0]), U14.13 (2DAT[0]), X1.7 (DAT0)
unnamed: R42.1, U11.19 (1DAT[1]), U14.12 (2DAT[1]), X1.8 (DAT1)
unnamed: IC4.2 (I1), IC7.1 (CLK), R4.1, R13.2, WD_RES_A.TP, W_RES_A.P$1
unnamed: IC5.2 (I1), IC7.13 (CLK), R6.1, R14.2, WD_RES_B.TP, W_RES_B.P$1
unnamed: IC5.1 (I0), IC6.4 (O), R89.1, R91.2
unnamed: R48.1, U11.17 (2DAT[3]), U14.24 (1DAT[3]), X2.2 (CD/DAT3)
unnamed: R50.1, U11.16 (2CMD), U14.23 (1CMD), X2.3 (CMD)
unnamed: U11.14 (2CLK), U14.21 (1CLK), X2.5 (CLK)
unnamed: R51.1, U11.13 (2DAT[0]), U14.20 (1DAT[0]), X2.7 (DAT0)
unnamed: R13.1, U5.1 (~RESET)
unnamed: R14.1, U6.1 (~RESET)
unnamed: R52.1, U11.12 (2DAT[1]), U14.19 (1DAT[1]), X2.8 (DAT1)
unnamed: R49.1, U11.18 (2DAT[2]), U14.1 (1DAT[2]), X2.1 (DAT2)
unnamed: R44.1, U4.18 (2DAT[2]), U13.1 (1DAT[2]), X5.1 (DAT2)
unnamed: R43.1, U4.17 (2DAT[3]), U13.24 (1DAT[3]), X5.2 (CD/DAT3)
unnamed: R45.1, U4.16 (2CMD), U13.23 (1CMD), X5.3 (CMD)
unnamed: U4.14 (2CLK), U13.21 (1CLK), X5.5 (CLK)
unnamed: R46.1, U4.13 (2DAT[0]), U13.20 (1DAT[0]), X5.7 (DAT0)
unnamed: R47.1, U4.12 (2DAT[1]), U13.19 (1DAT[1]), X5.8 (DAT1)
unnamed: R53.1, U4.24 (1DAT[3]), U13.17 (2DAT[3]), X6.2 (CD/DAT3)
unnamed: R55.1, U4.23 (1CMD), U13.16 (2CMD), X6.3 (CMD)
unnamed: U4.21 (1CLK), U13.14 (2CLK), X6.5 (CLK)
unnamed: R56.1, U4.20 (1DAT[0]), U13.13 (2DAT[0]), X6.7 (DAT0)
unnamed: R57.1, U4.19 (1DAT[1]), U13.12 (2DAT[1]), X6.8 (DAT1)
unnamed: R54.1, U4.1 (1DAT[2]), U13.18 (2DAT[2]), X6.1 (DAT2)
unnamed: R68.2, RPIA_SD_SEL.A
unnamed: R69.2, RPIB_SD_SEL.A
unnamed: R73.2, RPIA_RUN.A
unnamed: R74.2, RPIB_RUN.A
RPIA_MUX1_SD_CLK: U14.8 (CLK); also elsewhere on the board
RPIA_MUX1_SD_CMD: U14.5 (CMD); also elsewhere on the board
RPIA_MUX1_SD_D0: U14.9 (DAT[0]); also elsewhere on the board
RPIA_MUX1_SD_D1: U14.10 (DAT[1]); also elsewhere on the board
RPIA_MUX1_SD_D2: U14.3 (DAT[2]); also elsewhere on the board
RPIA_MUX1_SD_D3: U14.4 (DAT[3]); also elsewhere on the board
RPIA_MUX2_SD_CLK: U11.8 (CLK); also elsewhere on the board
RPIA_MUX2_SD_CMD: U11.5 (CMD); also elsewhere on the board
RPIA_MUX2_SD_D0: U11.9 (DAT[0]); also elsewhere on the board
RPIA_MUX2_SD_D1: U11.10 (DAT[1]); also elsewhere on the board
RPIA_MUX2_SD_D2: U11.3 (DAT[2]); also elsewhere on the board
RPIA_MUX2_SD_D3: U11.4 (DAT[3]); also elsewhere on the board
RPIA_RUN: C2.1, IC4.4 (O), PIA_RUN.P$1, R73.1; also elsewhere on the board
RPIA_SD_SEL: IC7.5 (Q), PIA_SD_SEL.P$1, R66.1, R68.1, U11.11 (S), U14.11 (S)
RPIB_MUX1_SD_CLK: U4.8 (CLK); also elsewhere on the board
RPIB_MUX1_SD_CMD: U4.5 (CMD); also elsewhere on the board
RPIB_MUX1_SD_D0: U4.9 (DAT[0]); also elsewhere on the board
RPIB_MUX1_SD_D1: U4.10 (DAT[1]); also elsewhere on the board
RPIB_MUX1_SD_D2: U4.3 (DAT[2]); also elsewhere on the board
RPIB_MUX1_SD_D3: U4.4 (DAT[3]); also elsewhere on the board
RPIB_MUX2_SD_CLK: U13.8 (CLK); also elsewhere on the board
RPIB_MUX2_SD_CMD: U13.5 (CMD); also elsewhere on the board
RPIB_MUX2_SD_D0: U13.9 (DAT[0]); also elsewhere on the board
RPIB_MUX2_SD_D1: U13.10 (DAT[1]); also elsewhere on the board
RPIB_MUX2_SD_D2: U13.3 (DAT[2]); also elsewhere on the board
RPIB_MUX2_SD_D3: U13.4 (DAT[3]); also elsewhere on the board
RPIB_RUN: C1.1, IC5.4 (O), PIB_RUN.P$1, R74.1; also elsewhere on the board
RPIB_SD_SEL: IC7.9 (Q), PIB_SD_SEL.P$1, R67.1, R69.1, U4.11 (S), U13.11 (S)
RPI_PWR_SEL: IC4.1 (I0), IC6.2 (I), PI_PWR_SEL.P$1, R3.1, R5.1, R7.1, R88.1; also elsewhere on the board
WD_A_WDI: U5.4 (WDI), WD_A_WDI.TP; also elsewhere on the board
WD_B_WDI: U6.4 (WDI), WD_B_WDI.TP; also elsewhere on the board

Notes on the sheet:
Filter noise on run line; soft shutdown
route close to RPI!
ensure RESET is buffered

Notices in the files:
parts and their libraries:
USB_c_conn: Copyright: Würth Elektronik
SparkFun-Jumpers: Licensing: Creative Commons ShareAlike 4.0 International - https://creativecommons.org/licenses/by-sa/4.0
COPYRIGHT: Copyright (C) 2018 Accelerated Designs. All rights reserved
